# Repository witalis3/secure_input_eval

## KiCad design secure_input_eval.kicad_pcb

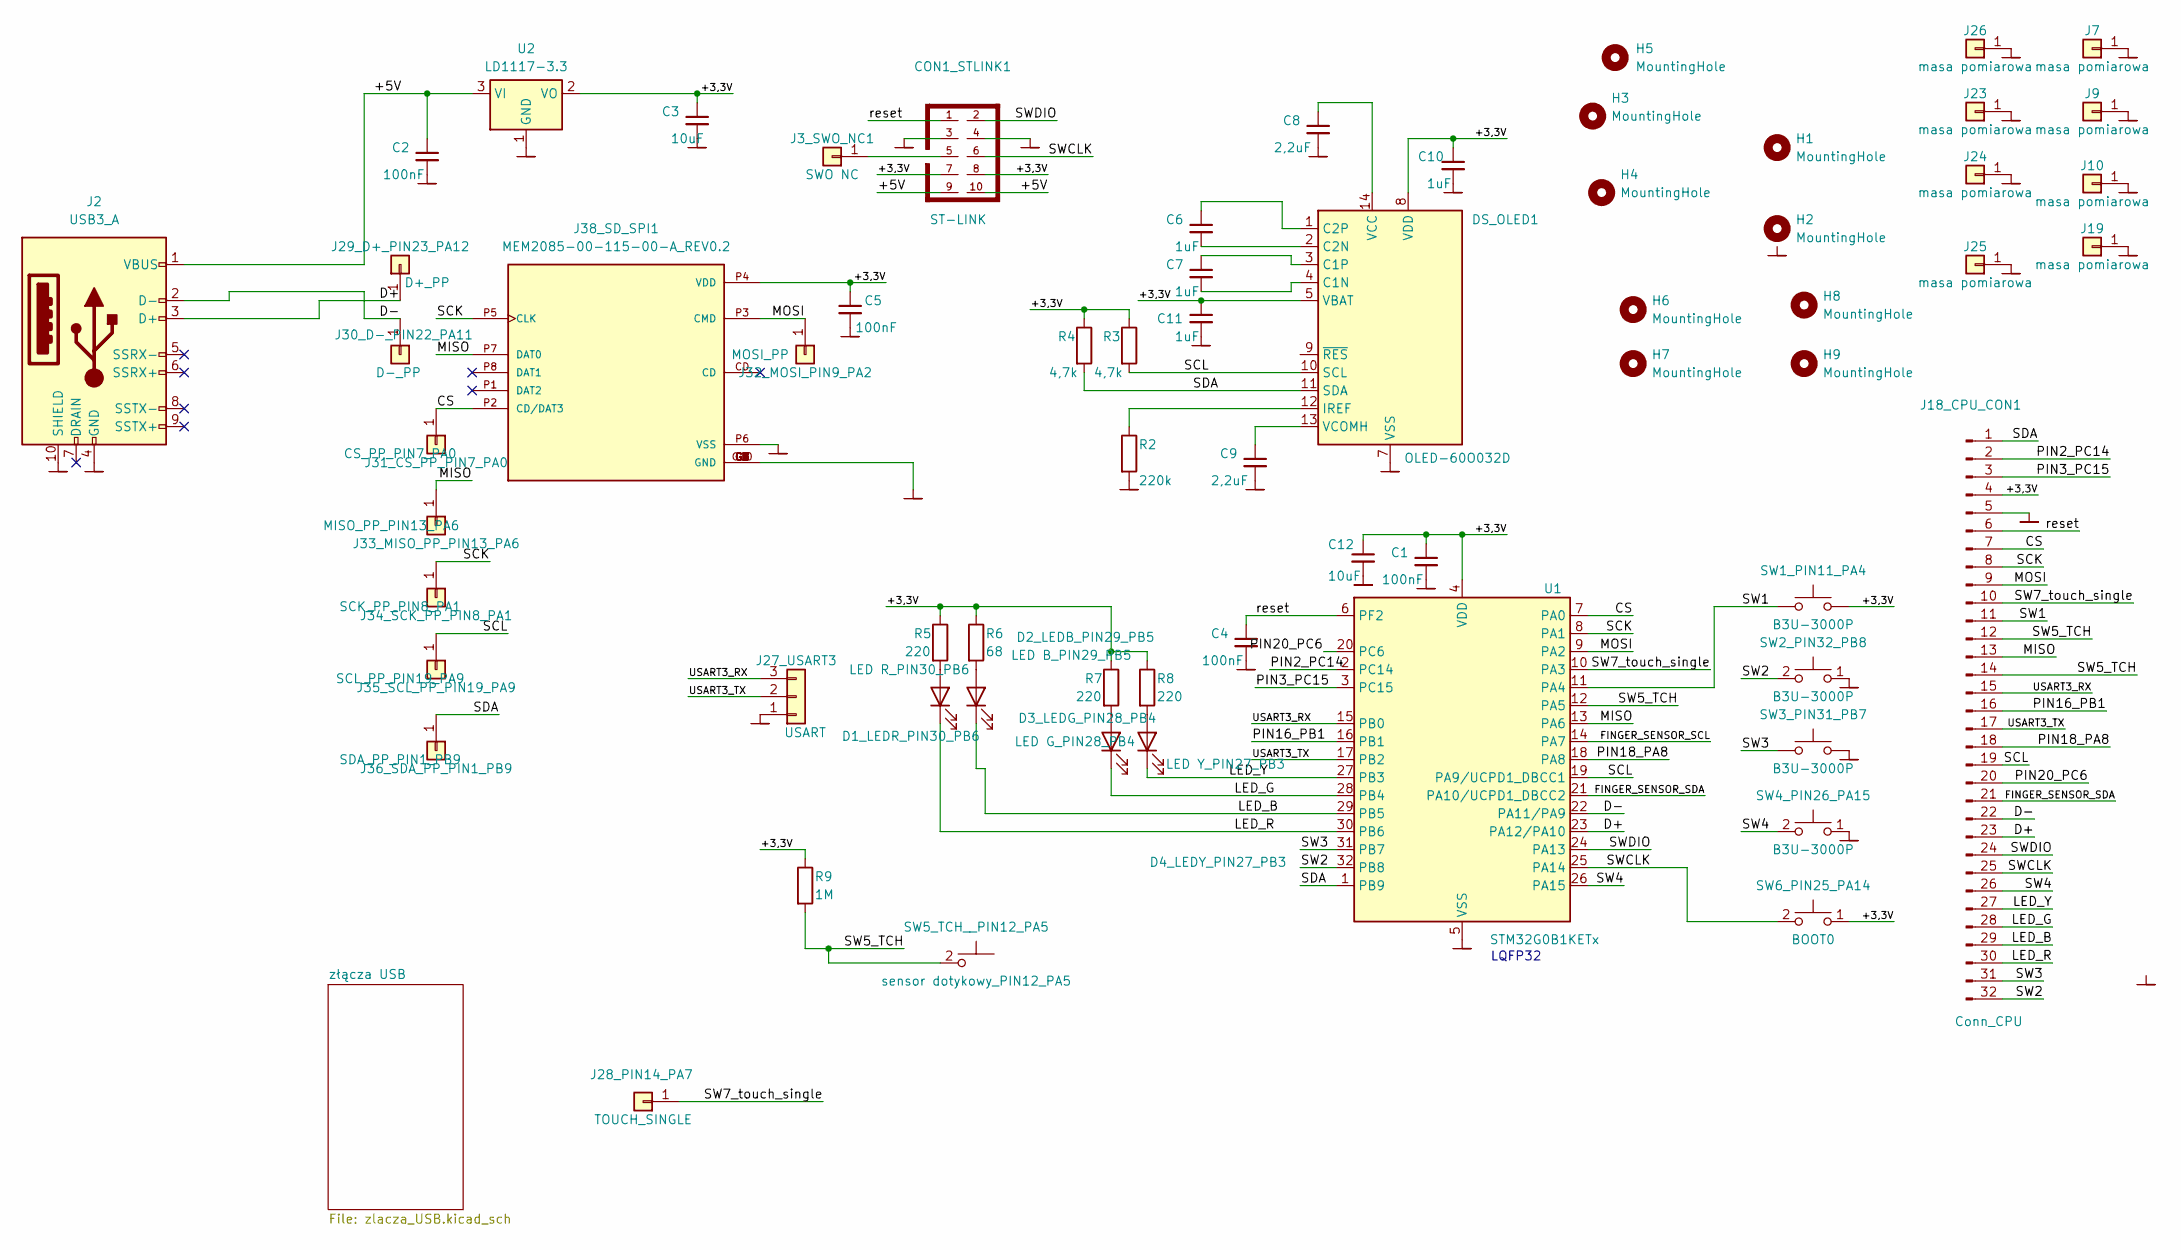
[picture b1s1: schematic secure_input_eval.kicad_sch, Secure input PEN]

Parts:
C1, C2, C4, C5: 100nF; C_0805_2012Metric_Pad1.18x1.45mm_HandSolder
C3, C12: 10uF; C_0805_2012Metric_Pad1.18x1.45mm_HandSolder
C6, C7, C10, C11: 1uF; C_0805_2012Metric_Pad1.18x1.45mm_HandSolder
C8, C9: 2,2uF; C_0805_2012Metric_Pad1.18x1.45mm_HandSolder
CON1_STLINK1: ST-LINK; IDC-10_wieksze_pady
D1_LEDR_PIN30_PB6: LED R_PIN30_PB6; LED_D3.0mm_Clear
D2_LEDB_PIN29_PB5: LED B_PIN29_PB5; LED_D3.0mm_Clear
D3_LEDG_PIN28_PB4: LED G_PIN28_PB4; LED_D3.0mm_Clear
D4_LEDY_PIN27_PB3: LED Y_PIN27_PB3; LED_D3.0mm_Clear
DS_OLED1: OLED-60O032D
H1, H2, H3, H4, H6, H7, H8, H9: MountingHole; MountingHole_3.2mm_M3
H5: MountingHole; MountingHole_2mm
J2: USB3_A; USB3_A_Amphenol_GSB316441CEU
J3_SWO_NC1: SWO NC; 1_PIN
J7, J9, J10, J19, J23, J24, J25, J26: masa pomiarowa; masa_pomiarowa
J18_CPU_CON1: Conn_CPU; PinSocket_1x32_P2.54mm_Vertical
J27_USART3: USART; PINHEAD-3
J28_PIN14_PA7: TOUCH_SINGLE; conn_touch_single
J29_D+_PIN23_PA12: D+_PP; 1_PIN
J30_D-_PIN22_PA11: D-_PP; 1_PIN
J31_CS_PP_PIN7_PA0: CS_PP_PIN7_PA0; 1_PIN
J32_MOSI_PIN9_PA2: MOSI_PP; 1_PIN
J33_MISO_PP_PIN13_PA6: MISO_PP_PIN13_PA6; 1_PIN
J34_SCK_PP_PIN8_PA1: SCK_PP_PIN8_PA1; 1_PIN
J35_SCL_PP_PIN19_PA9: SCL_PP_PIN19_PA9; 1_PIN
J36_SDA_PP_PIN1_PB9: SDA_PP_PIN1_PB9; 1_PIN
J38_SD_SPI1: MEM2085-00-115-00-A_REV0.2; GCT_MEM2085-00-115-00-A_REV0.2; PARTREV 0.2
R2: 220k; R_0805_2012Metric_Pad1.20x1.40mm_HandSolder
R3, R4: 4,7k; R_0805_2012Metric_Pad1.20x1.40mm_HandSolder
R5, R7, R8: 220; R_0805_2012Metric_Pad1.20x1.40mm_HandSolder
R6: 68; R_0805_2012Metric_Pad1.20x1.40mm_HandSolder
R9: 1M; R_0805_2012Metric_Pad1.20x1.40mm_HandSolder
SW1_PIN11_PA4, SW2_PIN32_PB8, SW3_PIN31_PB7, SW4_PIN26_PA15: B3U-3000P; SW_PUSH_6mm_H4.3mm
SW5_TCH__PIN12_PA5: sensor dotykowy_PIN12_PA5; conn_touch
SW6_PIN25_PA14: BOOT0; SW_PUSH_6mm_H4.3mm
U1: STM32G0B1KETx; LQFP-32_7x7mm_P0.8mm
U2: LD1117-3.3; SOT-223-3_TabPin2

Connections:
/+3,3V: C1.1, C3.1, C5.1, C10.1, C11.1, C12.1, CON1_STLINK1.7, CON1_STLINK1.8, DS_OLED1.5 (VBAT), DS_OLED1.8 (VDD), J18_CPU_CON1.4, J38_SD_SPI1.P4 (VDD), R3.1, R4.1, R5.1, R6.1, R7.1, R8.1, R9.1, SW1_PIN11_PA4.2, SW6_PIN25_PA14.1, U1.4 (VDD), U2.2 (VO)
/+5V: C2.1, CON1_STLINK1.9, CON1_STLINK1.10, J2.1 (VBUS), U2.3 (VI)
/CS: J18_CPU_CON1.7, J31_CS_PP_PIN7_PA0.1, J38_SD_SPI1.P2 (CD/DAT3), U1.7 (PA0)
/D+: J2.3 (D+), J18_CPU_CON1.23, J29_D+_PIN23_PA12.1, U1.23 (PA12/PA10)
/D-: J2.2 (D-), J18_CPU_CON1.22, J30_D-_PIN22_PA11.1, U1.22 (PA11/PA9)
/FINGER_SENSOR_SCL: U1.14 (PA7)
/FINGER_SENSOR_SDA: J18_CPU_CON1.21, U1.21 (PA10/UCPD1_DBCC2)
/LED_B: D2_LEDB_PIN29_PB5.1 (K), J18_CPU_CON1.29, U1.29 (PB5)
/LED_G: D3_LEDG_PIN28_PB4.1 (K), J18_CPU_CON1.28, U1.28 (PB4)
/LED_R: D1_LEDR_PIN30_PB6.1 (K), J18_CPU_CON1.30, U1.30 (PB6)
/LED_Y: D4_LEDY_PIN27_PB3.1 (K), J18_CPU_CON1.27, U1.27 (PB3)
/MISO: J18_CPU_CON1.13, J33_MISO_PP_PIN13_PA6.1, J38_SD_SPI1.P7 (DAT0), U1.13 (PA6)
/MOSI: J18_CPU_CON1.9, J32_MOSI_PIN9_PA2.1, J38_SD_SPI1.P3 (CMD), U1.9 (PA2)
/PIN2_PC14: J18_CPU_CON1.2, U1.2 (PC14)
/PIN3_PC15: J18_CPU_CON1.3, U1.3 (PC15)
/PIN16_PB1: J18_CPU_CON1.16, U1.16 (PB1)
/PIN18_PA8: J18_CPU_CON1.18, U1.18 (PA8)
/PIN20_PC6: J18_CPU_CON1.20, U1.20 (PC6)
/SCK: J18_CPU_CON1.8, J34_SCK_PP_PIN8_PA1.1, J38_SD_SPI1.P5 (CLK), U1.8 (PA1)
/SCL: DS_OLED1.10 (SCL), J18_CPU_CON1.19, J35_SCL_PP_PIN19_PA9.1, R3.2, U1.19 (PA9/UCPD1_DBCC1)
/SDA: DS_OLED1.11 (SDA), J18_CPU_CON1.1, J36_SDA_PP_PIN1_PB9.1, R4.2, U1.1 (PB9)
/SW1: J18_CPU_CON1.11, SW1_PIN11_PA4.1, U1.11 (PA4)
/SW2: J18_CPU_CON1.32, SW2_PIN32_PB8.2, U1.32 (PB8)
/SW3: J18_CPU_CON1.31, SW3_PIN31_PB7.1, U1.31 (PB7)
/SW4: J18_CPU_CON1.26, SW4_PIN26_PA15.2, U1.26 (PA15)
/SW5_TCH: J18_CPU_CON1.12, J18_CPU_CON1.14, R9.2, SW5_TCH__PIN12_PA5.2, U1.12 (PA5)
/SW7_touch_single: J18_CPU_CON1.10, J28_PIN14_PA7.1, U1.10 (PA3)
/SWCLK: CON1_STLINK1.6, J18_CPU_CON1.25, SW6_PIN25_PA14.2, U1.25 (PA14)
/SWDIO: CON1_STLINK1.2, J18_CPU_CON1.24, U1.24 (PA13)
/USART3_RX: J18_CPU_CON1.15, J27_USART3.3, U1.15 (PB0)
/USART3_TX: J18_CPU_CON1.17, J27_USART3.2, U1.17 (PB2)
/reset: C4.1, CON1_STLINK1.1, J18_CPU_CON1.6, U1.6 (PF2)
unnamed: D1_LEDR_PIN30_PB6.2 (A), R5.2
unnamed: D2_LEDB_PIN29_PB5.2 (A), R6.2
unnamed: D3_LEDG_PIN28_PB4.2 (A), R7.2
unnamed: D4_LEDY_PIN27_PB3.2 (A), R8.2
unnamed: C7.2, DS_OLED1.4 (C1N)
unnamed: C7.1, DS_OLED1.3 (C1P)
unnamed: C6.2, DS_OLED1.2 (C2N)
unnamed: C6.1, DS_OLED1.1 (C2P)
unnamed: DS_OLED1.12 (IREF), R2.1
unnamed: C8.1, DS_OLED1.14 (VCC)
unnamed: C9.1, DS_OLED1.13 (VCOMH)
unnamed: CON1_STLINK1.5, J3_SWO_NC1.1
masa: C1.2, C2.2, C3.2, C4.2, C5.2, C8.2, C9.2, C10.2, C11.2, C12.2, CON1_STLINK1.3, CON1_STLINK1.4, DS_OLED1.7 (VSS), J2.4 (GND), J2.10 (SHIELD), J7.1, J9.1, J10.1, J18_CPU_CON1.5, J19.1, J23.1, J24.1, J25.1, J26.1, J27_USART3.1, J38_SD_SPI1.G1 (GND), J38_SD_SPI1.G2 (GND), J38_SD_SPI1.G3 (GND), J38_SD_SPI1.G4 (GND), J38_SD_SPI1.G5 (GND), J38_SD_SPI1.G6 (GND), J38_SD_SPI1.G7 (GND), J38_SD_SPI1.G8 (GND), J38_SD_SPI1.G9 (GND), J38_SD_SPI1.G10 (GND), J38_SD_SPI1.P6 (VSS), R2.2, SW2_PIN32_PB8.1, SW3_PIN31_PB7.2, SW4_PIN26_PA15.1, U1.5 (VSS), U2.1 (GND)

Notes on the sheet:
LQFP32

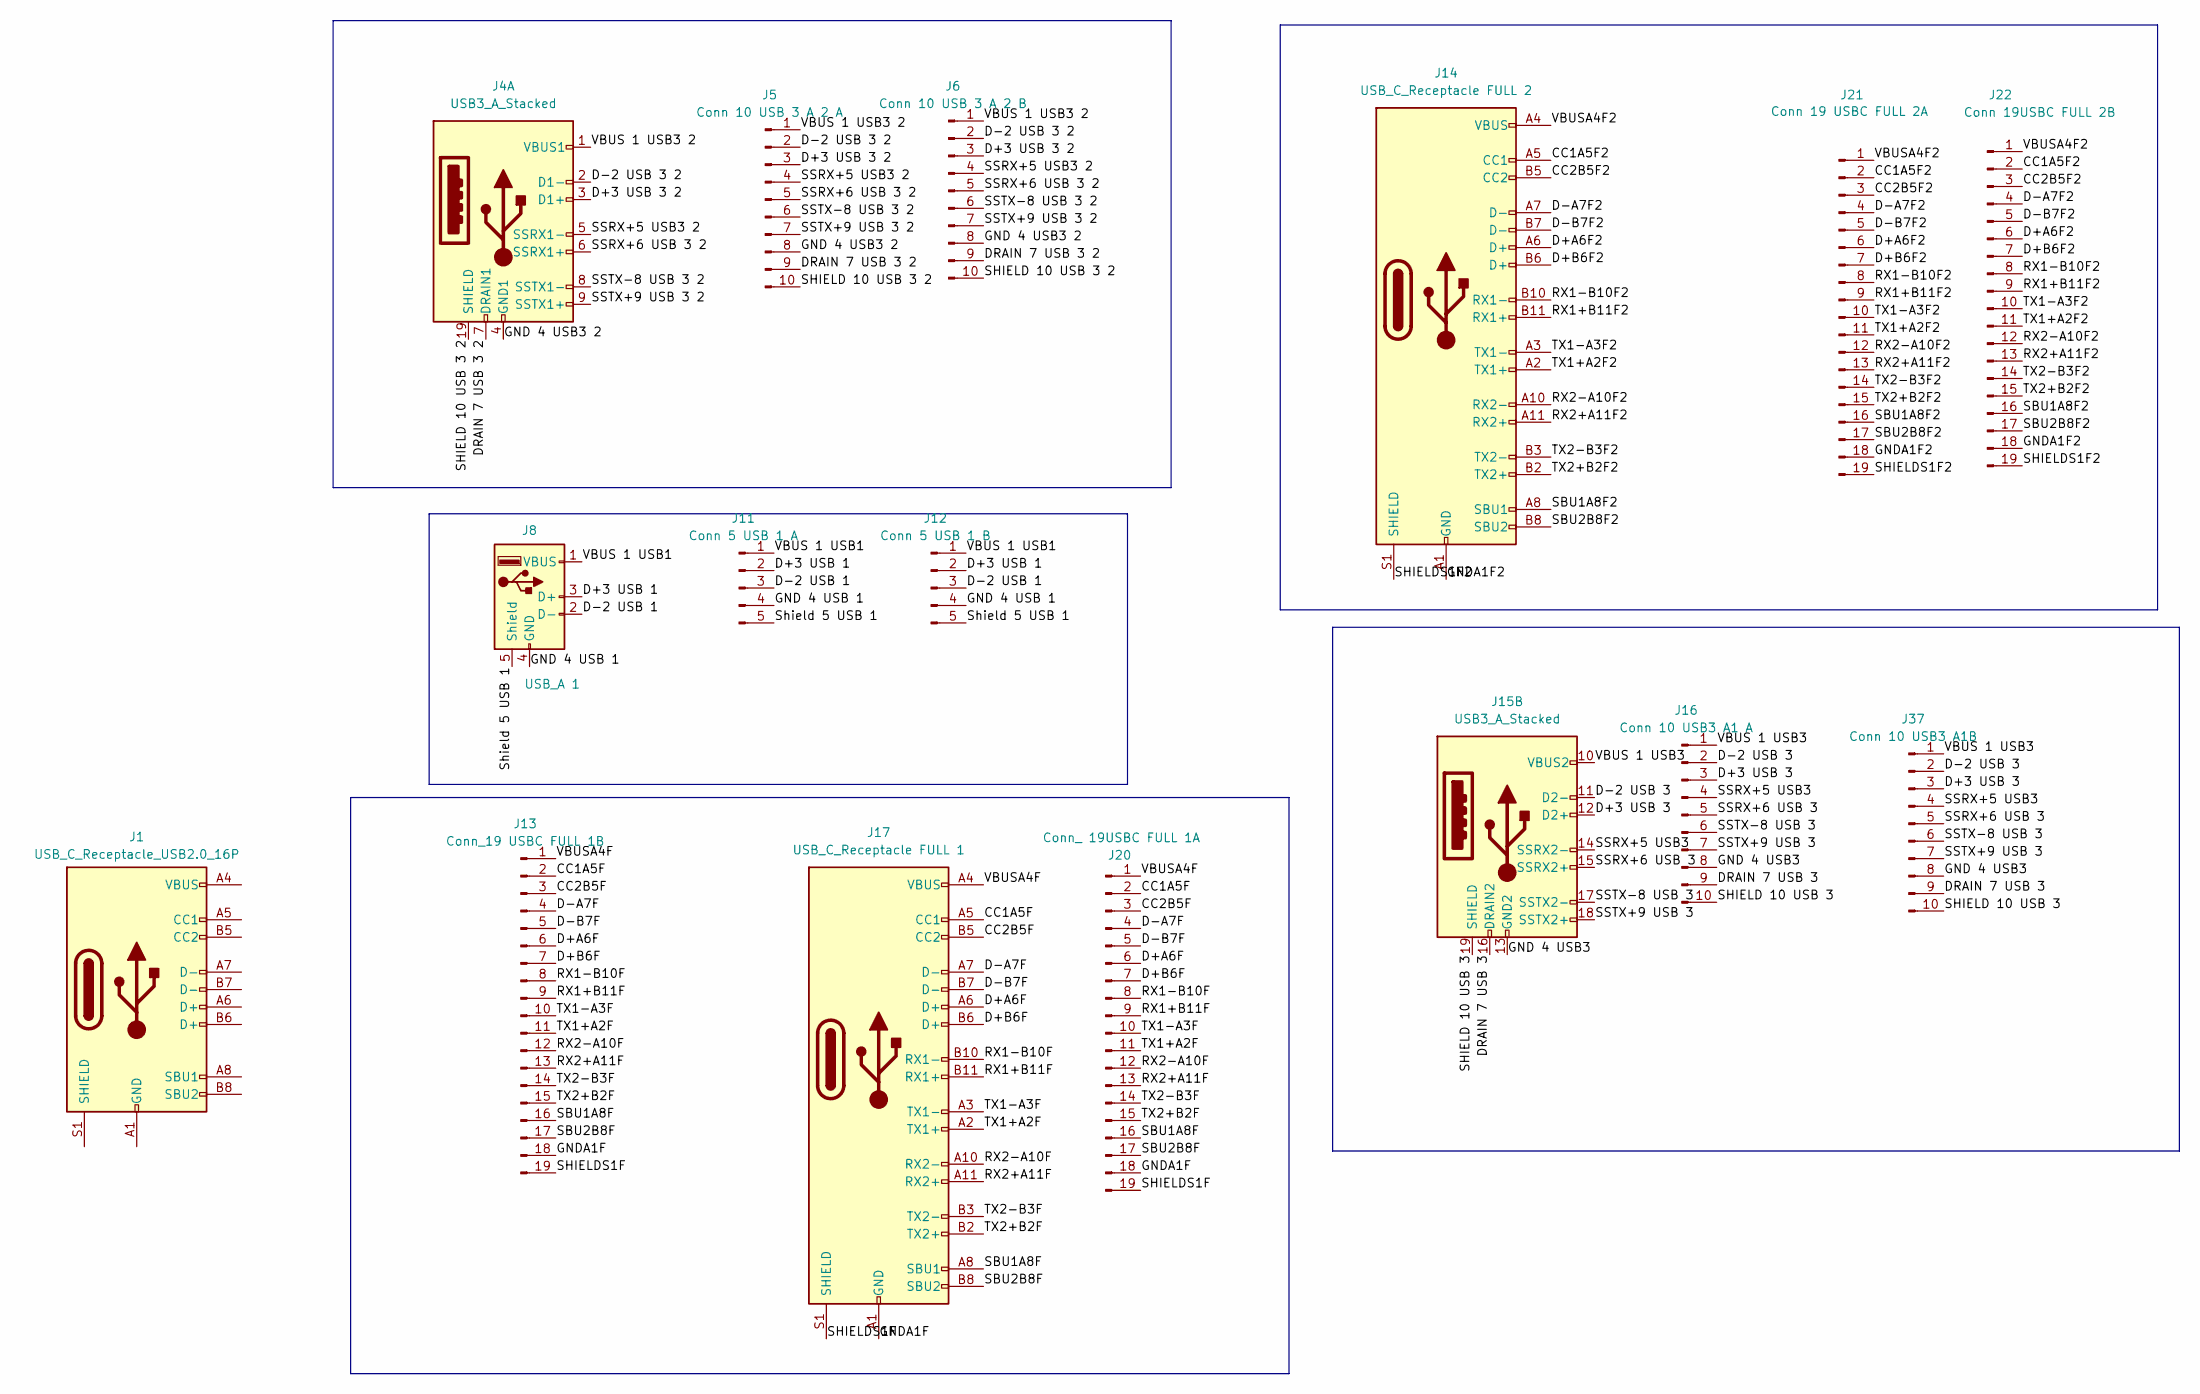
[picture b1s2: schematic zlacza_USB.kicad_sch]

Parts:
J1: USB_C_Receptacle_USB2.0_16P; USB_C_Receptacle_G-Switch_GT-USB-7010ASV
J4, J15: USB3_A_Stacked; USB3_A_Molex_48406-0001_Horizontal_Stacked
J5: Conn 10 USB 3 A 2 A; PinHeader_1x10_P2.54mm_Vertical
J6: Conn 10 USB 3 A 2 B; PinHeader_1x10_P2.54mm_Vertical
J8: USB_A 1; USB_A_Connfly_DS1095
J11: Conn 5 USB 1 A; PinHeader_1x05_P2.54mm_Vertical
J12: Conn 5 USB 1 B; PinHeader_1x05_P2.54mm_Vertical
J13: Conn_19 USBC FULL 1B; PinHeader_1x19_P2.54mm_Vertical
J14: USB_C_Receptacle FULL 2; USB_C_Receptacle_Amphenol_12401548E4-2A
J16: Conn 10 USB3 A1 A; PinHeader_1x10_P2.54mm_Vertical
J17: USB_C_Receptacle FULL 1; USB_C_Receptacle_Amphenol_12401548E4-2A
J20: Conn_ 19USBC FULL 1A; PinHeader_1x19_P2.54mm_Vertical
J21: Conn 19 USBC FULL 2A; PinHeader_1x19_P2.54mm_Vertical
J22: Conn 19USBC FULL 2B; PinHeader_1x19_P2.54mm_Vertical
J37: Conn 10 USB3 A1B; PinHeader_1x10_P2.54mm_Vertical

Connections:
/złącza USB/CC1A5F: J13.2, J17.A5 (CC1), J20.2
/złącza USB/CC1A5F2: J14.A5 (CC1), J21.2, J22.2
/złącza USB/CC2B5F: J13.3, J17.B5 (CC2), J20.3
/złącza USB/CC2B5F2: J14.B5 (CC2), J21.3, J22.3
/złącza USB/D+3 USB 1: J8.3 (D+), J11.2, J12.2
/złącza USB/D+3 USB 3: J15.12 (D2+), J16.3, J37.3
/złącza USB/D+3 USB 3 2: J4.3 (D1+), J5.3, J6.3
/złącza USB/D+A6F: J13.6, J17.A6 (D+), J20.6
/złącza USB/D+A6F2: J14.A6 (D+), J21.6, J22.6
/złącza USB/D+B6F: J13.7, J17.B6 (D+), J20.7
/złącza USB/D+B6F2: J14.B6 (D+), J21.7, J22.7
/złącza USB/D-2 USB 1: J8.2 (D-), J11.3, J12.3
/złącza USB/D-2 USB 3: J15.11 (D2-), J16.2, J37.2
/złącza USB/D-2 USB 3 2: J4.2 (D1-), J5.2, J6.2
/złącza USB/D-A7F: J13.4, J17.A7 (D-), J20.4
/złącza USB/D-A7F2: J14.A7 (D-), J21.4, J22.4
/złącza USB/D-B7F: J13.5, J17.B7 (D-), J20.5
/złącza USB/D-B7F2: J14.B7 (D-), J21.5, J22.5
/złącza USB/DRAIN 7 USB 3: J15.16 (DRAIN2), J16.9, J37.9
/złącza USB/DRAIN 7 USB 3 2: J4.7 (DRAIN1), J5.9, J6.9
/złącza USB/GND 4 USB3: J15.13 (GND2), J16.8, J37.8
/złącza USB/GND 4 USB3 2: J4.4 (GND1), J5.8, J6.8
/złącza USB/GND 4 USB 1: J8.4 (GND), J11.4, J12.4
/złącza USB/GNDA1F: J13.18, J17.A1 (GND), J17.A12 (GND), J17.B1 (GND), J17.B12 (GND), J20.18
/złącza USB/GNDA1F2: J14.A1 (GND), J14.A12 (GND), J14.B1 (GND), J14.B12 (GND), J21.18, J22.18
/złącza USB/RX1+B11F: J13.9, J17.B11 (RX1+), J20.9
/złącza USB/RX1+B11F2: J14.B11 (RX1+), J21.9, J22.9
/złącza USB/RX1-B10F: J13.8, J17.B10 (RX1-), J20.8
/złącza USB/RX1-B10F2: J14.B10 (RX1-), J21.8, J22.8
/złącza USB/RX2+A11F: J13.13, J17.A11 (RX2+), J20.13
/złącza USB/RX2+A11F2: J14.A11 (RX2+), J21.13, J22.13
/złącza USB/RX2-A10F: J13.12, J17.A10 (RX2-), J20.12
/złącza USB/RX2-A10F2: J14.A10 (RX2-), J21.12, J22.12
/złącza USB/SBU1A8F: J13.16, J17.A8 (SBU1), J20.16
/złącza USB/SBU1A8F2: J14.A8 (SBU1), J21.16, J22.16
/złącza USB/SBU2B8F: J13.17, J17.B8 (SBU2), J20.17
/złącza USB/SBU2B8F2: J14.B8 (SBU2), J21.17, J22.17
/złącza USB/SHIELD 10 USB 3: J15.19 (SHIELD), J16.10, J37.10
/złącza USB/SHIELD 10 USB 3 2: J4.19 (SHIELD), J5.10, J6.10
/złącza USB/SHIELDS1F: J13.19, J17.S1 (SHIELD), J20.19
/złącza USB/SHIELDS1F2: J14.S1 (SHIELD), J21.19, J22.19
/złącza USB/SSRX+5 USB3: J15.14 (SSRX2-), J16.4, J37.4
/złącza USB/SSRX+5 USB3 2: J4.5 (SSRX1-), J5.4, J6.4
/złącza USB/SSRX+6 USB 3: J15.15 (SSRX2+), J16.5, J37.5
/złącza USB/SSRX+6 USB 3 2: J4.6 (SSRX1+), J5.5, J6.5
/złącza USB/SSTX+9 USB 3: J15.18 (SSTX2+), J16.7, J37.7
/złącza USB/SSTX+9 USB 3 2: J4.9 (SSTX1+), J5.7, J6.7
/złącza USB/SSTX-8 USB 3: J15.17 (SSTX2-), J16.6, J37.6
/złącza USB/SSTX-8 USB 3 2: J4.8 (SSTX1-), J5.6, J6.6
/złącza USB/Shield 5 USB 1: J8.5 (Shield), J11.5, J12.5
/złącza USB/TX1+A2F: J13.11, J17.A2 (TX1+), J20.11
/złącza USB/TX1+A2F2: J14.A2 (TX1+), J21.11, J22.11
/złącza USB/TX1-A3F: J13.10, J17.A3 (TX1-), J20.10
/złącza USB/TX1-A3F2: J14.A3 (TX1-), J21.10, J22.10
/złącza USB/TX2+B2F: J13.15, J17.B2 (TX2+), J20.15
/złącza USB/TX2+B2F2: J14.B2 (TX2+), J21.15, J22.15
/złącza USB/TX2-B3F: J13.14, J17.B3 (TX2-), J20.14
/złącza USB/TX2-B3F2: J14.B3 (TX2-), J21.14, J22.14
/złącza USB/VBUS 1 USB1: J8.1 (VBUS), J11.1, J12.1
/złącza USB/VBUS 1 USB3: J15.10 (VBUS2), J16.1, J37.1
/złącza USB/VBUS 1 USB3 2: J4.1 (VBUS1), J5.1, J6.1
/złącza USB/VBUSA4F: J13.1, J17.A4 (VBUS), J17.A9 (VBUS), J17.B4 (VBUS), J17.B9 (VBUS), J20.1
/złącza USB/VBUSA4F2: J14.A4 (VBUS), J14.A9 (VBUS), J14.B4 (VBUS), J14.B9 (VBUS), J21.1, J22.1
unnamed: J1.A1 (GND), J1.A12 (GND), J1.B1 (GND), J1.B12 (GND)
unnamed: J1.A4 (VBUS), J1.A9 (VBUS), J1.B4 (VBUS), J1.B9 (VBUS)

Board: 6 copper layers, 81 parts (26 on the bottom side), 109 nets, no tracks yet.

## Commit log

2025-06-09 osobne repo dla wspierajacego projektu
2025-06-10 Test Commit. To be deletedfile.
2025-06-14 Update conector usb.
2025-06-14 Test file deleted.
2025-06-15 Cutting two bards drill-holes.
2025-06-15 TITLES&SUBTITLES POSITIONS & NAMES.
2025-06-15 Prepare to CHECK ToDo.txt / EVAL >< PEN
2025-06-17 symbole i footprinty #1
